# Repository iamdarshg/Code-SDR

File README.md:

# Code-SDR — V2 wideband SDR

A single-board, 100 MHz – 10 GHz receiver with an FPGA gateware datapath, an
RP2040 controller, and host-side tooling.

**Current hardware is V2:** the modular receiver/control board in
[`hardware/v2`](hardware/v2). The first-generation `Wideband-Test-V1` design was
audited and found **unsafe to fabricate**; its RTL, firmware, software and design
documents have been removed from this tree. What remains of V1 is the audit
record and clearly-labelled history — see
[V1 / legacy status](#v1--legacy-status).

> **Status, stated plainly.** No board has been fabricated and nothing in this
> repository has touched silicon. All gateware claims below are simulation and
> synthesis estimates. Frame counts, pin constraints and vendor I/O primitives
> still need Lattice Diamond and a first article. See
> [`GATEWARE.md`](GATEWARE.md), [`RESOURCE_REPORT.md`](RESOURCE_REPORT.md) and
> [`BRINGUP.md`](BRINGUP.md).

---

## Hardware at a glance

Source of truth is copper:
[`hardware/v2/Code-SDR-V2.kicad_pcb`](hardware/v2/Code-SDR-V2.kicad_pcb), parsed
in [`HARDWARE.md`](HARDWARE.md). 99 × 99 mm, four copper layers, 373 placed
footprints.

| Block | Part | Role |
|---|---|---|
| Controller | RP2040 (U10) + W25Q16JV QSPI flash | Sole controller: SPI master, FPGA config, USB CDC telemetry |
| FPGA | LIF-MD6000-6JMG80I (U20) | 5,936 LUT4, 180 kbit EBR, no DSP blocks |
| ADC | AD9215BCPZ-105 (U21) | 10-bit parallel, clocked from the fixed 100 MHz board reference — i.e. **100 MSPS**. `-105` is the part rating, not the operating rate |
| Ethernet | KSZ9031RNXCA (U30), RJ45 with magnetics | **RGMII only** — there is no GMII on this PCB |
| Reference | SiT8209 100 MHz (Y40) → CDCLVC1104 fanout | Shared ADC + synthesiser reference; PHY keeps its own 25 MHz crystal |
| Synthesisers | LMX2592 (U40), ADF4360-1 (U41) | First and second LO |
| RF front end | 5 SMA lanes, GRF LNAs, ADL5801 / LTC5548 / LT5560 mixers | 100 MHz – 10 GHz, 40 MHz real IBW, 2436.25 MHz IF1 → 26.25 MHz ADC IF |
| Power | 5 V in only (J1), TLV62569 bucks + TPS7A8300 LNA | ≈ 6.6 W estimated, ≈ 5 W of it the RF rail — see [`POWER.md`](POWER.md) |

USB on this board is **data/control only**; there is no USB-powered or USB-bulk
SDR streaming path.

## Gateware at a glance

Two **compile-time exclusive** modes (`v2_top` builds one or the other; the
RP2040 holds both bitstreams and swaps them over SPI in ~0.1–0.2 s):

```
MODE = 0 (raw)   ADC 100 MSPS -> 8/10-bit pack -> CDC FIFO -> UDP/IP -> MAC -> RGMII
MODE = 1 (fft)   ADC 100 MSPS -> CIC /R -> CDC FIFO -> window -> N-pt FFT
                             -> bin packetizer -> UDP/IP -> MAC -> RGMII
```

| | Raw (MODE=0) | FFT (MODE=1) |
|---|---|---|
| Area | **2,400 / 5,936 LUT4** (Yosys + ABC) | not yet measurable; bounded analytically |
| Verified throughput | 801 Mbps wire at 8-bit / 100 MSPS, no drops | 7.8 MSPS sustained input at N=1024 |
| Host does | FFT, demod, recording | display only |

10-bit at 100 MSPS offers 1002 Mbps, which no gigabit link carries, so raw mode
keeps the full rate and drops ~0.9 % of **whole datagrams** via a delta-sigma
accumulator (exact `floor(K·frac/65536)` drop count, verified to the packet). Loss
is counted and reported in-band, never hidden. Full detail, including the CIC /
FFT rate table and the three real FFT bugs found: [`GATEWARE.md`](GATEWARE.md).

## Repository map

| Path | What it is |
|---|---|
| `hardware/v2/` | **V2 board source of truth** — KiCad 9 project, 8 schematic sheets, footprints, deterministic generators in `tools/` |
| `hardware/redesign/` | Frequency plan, noise/filter budgets, power tree, V1↔V2 BOM cost model (reproducible Python) |
| `hardware/HARDWARE_VALIDATION.md` | Why V1 is DO NOT FABRICATE; the implemented V2 architecture |
| `hardware/validate_hardware.ps1` | Runs the ERC/DRC audit against the V2 project |
| `hardware/KSZ9031RNXCC-TR/`, `hardware/MABA-011108/` | Vendored KiCad vendor libraries (retained, see cleanup report) |
| `verilog/` | V2 gateware `v2_*.v`, testbenches, `v2_top.lpf`, `sim/crosslink_prims_sim.v` |
| `firmware/rp2040_dashboard/` | The RP2040 sketch: SPI telemetry, fault engine, bitstream swap |
| `software/` | Host tools: `sdr_spectrum.py`, `sdr_dashboard.py`, shared `sdr_common.py` |
| `tools/` | `run_tests.py`, `lint_verilog.py`, `check_firmware.py`, `gen_lpf.py`, `gen_twiddles.py`, `r2sdf_reference.py` |
| `tests/` | One retained cocotb test (`async_fifo`); the real regression is `tools/run_tests.py` |
| `docs/em-validation/` | EM/RF validation proof package (analytical, fail-closed) |
| `docs/superpowers/` | Routing plans and specs behind the V2 copper |
| `reviews/`, `outputs/code-sdr-routing/` | V2 routing review records and routing deliverables |
| `openfpga_framework/` | Vendored upstream OpenFPGA framework — retained, not used by the V2 build (see cleanup report) |
| `HARDWARE.md` / `GATEWARE.md` / `RESOURCE_REPORT.md` / `POWER.md` / `BRINGUP.md` / `KNOWN_ISSUES.md` | PCB-parse, gateware, area, power, bring-up and defect register |
| `docs/CLEANUP_2026-11-04.md` | The V1 removal / README cleanup record |

## Quick start

Requirements: Python 3.8+ with `numpy scipy matplotlib` for the host tools;
Icarus Verilog for the RTL regression; Verilator for the lint gate; `arduino-cli`
with the earlephilhower RP2040 core for the firmware build.

```bash
pip install numpy scipy matplotlib

# Host viewer — works with no radio attached
python software/sdr_spectrum.py --simulate --save spectrum.png --frames 20

# Live, against a configured board (both modes transmit to UDP 10000)
python software/sdr_spectrum.py --mode raw
python software/sdr_spectrum.py --mode fft
python software/sdr_dashboard.py --port 10000 --serial COM7

# Host-tool unit checks (run from the repository root)
python software/test_dashboard.py
```

## Verification

These are the gates CI runs (`.github/workflows/rtl.yml`), and they are the only
commands that should be quoted as "the tests pass":

```bash
python tools/run_tests.py        # Icarus regression: 21 testbench runs
python tools/lint_verilog.py     # Verilator lint: 5 tops
python tools/check_firmware.py   # arduino-cli compile of the RP2040 sketch
```

Last run of this tree (2026-11-04, Windows, Icarus Verilog 12.0, Verilator 5.040,
arduino-cli):

```
run_tests.py       21/21 passed
lint_verilog.py    5/5 tops clean
check_firmware.py  PASS: firmware compiles (0 warning(s))
```

Hardware analyses are reproducible too:

```bash
python hardware/redesign/validate_plan.py    # frequency plan / LO / Nyquist
python hardware/redesign/rf_analysis.py      # Friis cascade, NF, anti-alias
python hardware/redesign/cost_model.py       # V1 vs V2 fitted BOM
python tools/gen_lpf.py                      # PCB -> verilog/v2_top_generated.lpf
```

## Documentation

| Document | Contents |
|---|---|
| [`HARDWARE.md`](HARDWARE.md) | Every claim parsed from placed footprints, pad nets and PCB setup; supersedes all other hardware prose |
| [`hardware/HARDWARE_VALIDATION.md`](hardware/HARDWARE_VALIDATION.md) | V1 audit (ERC/DRC counts), V2 corrections, limitations, first-article plan |
| [`GATEWARE.md`](GATEWARE.md) | Two modes, rate plan, throughput table, FFT correctness, what blocks production |
| [`RESOURCE_REPORT.md`](RESOURCE_REPORT.md) | Yosys/ABC area numbers and what is still unmeasured |
| [`POWER.md`](POWER.md) | Per-rail load estimates and the one-lane-at-a-time policy |
| [`BRINGUP.md`](BRINGUP.md) | Staged board bring-up, each step with its failure signature |
| [`KNOWN_ISSUES.md`](KNOWN_ISSUES.md) | Defect register: fixed (kept for the record) and open |
| [`docs/em-validation/EM_VALIDATION_REPORT.md`](docs/em-validation/EM_VALIDATION_REPORT.md) | EM/RF evidence package; every full-wave/physical claim fails closed |
| [`software/LEGACY.md`](software/LEGACY.md) | What the four removed V1 software trees attempted |

## V1 / legacy status

The first-generation design (`Wideband-Test-V1`, dsPIC33 firmware, 105 MSPS /
GMII RTL, USB-bulk host stack, GNU Radio module, ExtIO plugin) is **removed from
this tree**. It is not supported, not buildable here, and its pin, clock and
interface claims must not be reused: see the void list at the top of
[`HARDWARE.md`](HARDWARE.md).

Where the record survives:

- `hardware/HARDWARE_VALIDATION.md` — the reproducible V1 audit, kept as evidence.
- [`software/LEGACY.md`](software/LEGACY.md) — what each removed software tree
  attempted and why it was abandoned.
- [`KNOWN_ISSUES.md`](KNOWN_ISSUES.md) § Removed — the deleted P0 RTL cluster,
  module by module.
- [`ISSUE_11_VERIFICATION_REPORT.md`](ISSUE_11_VERIFICATION_REPORT.md) — the V1
  integration report, retained but marked historical.
- `git log -- <path>` — every removed tree is recoverable from history.
- [`docs/CLEANUP_2026-11-04.md`](docs/CLEANUP_2026-11-04.md) — the itemised
  removal list from the 2026-11-04 cleanup.

Deliberately **not** removed: vendored third-party libraries and the upstream
OpenFPGA framework, which are not V1 design work. They are classified in the
cleanup report.

## Licence

This repository contains **no `LICENSE` file**. Treat it as all rights reserved
until one is added; the badges and MIT text that earlier revisions of this README
carried referred to a file that is not present.

## References

- Lattice CrossLink: FPGA-TN-02015 (sysCLOCK PLL), FPGA-TN-02016 (sysI/O),
  FPGA-TN-02012 (high-speed I/O) — needed to confirm the vendor primitives that
  `verilog/v2_clock_pll.v` and `verilog/v2_rgmii.v` instantiate behind
  `V2_USE_VENDOR_PLL` / `V2_USE_VENDOR_DDR`.
- Microchip KSZ9031RNX datasheet — RGMII delay registers used by
  `v2_phy_manager.v`.
- Analog Devices AD9215 datasheet — 10-bit parallel timing.

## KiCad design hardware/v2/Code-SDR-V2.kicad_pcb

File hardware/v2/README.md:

# Code-SDR V2 hardware

This is the modular KiCad 9 receiver/control-board redesign. It covers
100 MHz-10 GHz with 40 MHz useful real bandwidth. It is explicitly not an ESC;
the ESC remains a separate external board.

## Project structure

- `Code-SDR-V2.kicad_sch` - hierarchical root schematic.
- `sheets/` - eight functional subsheets.
- `Code-SDR-V2.kicad_pcb` - 99 x 99 mm, four-layer PCB with the 49 RF50
  controlled-impedance nets routed.
- `Code-SDR-V2.kicad_pro` and `.kicad_dru` - project and enforced rules.
- `CodeSDR.pretty/` and `CodeSDR.kicad_sym` - project-local audited libraries.
- `tools/design_model.py` - single electrical component/net contract.
- `tools/generate_schematic.py` and `tools/generate_pcb.py` - deterministic CAD
  generation.
- `build/` - validation and intermediate output; final manufacturing outputs
  are exported separately for release.

The FPGA supply islands and configuration pulls implement the Lattice
CrossLink hardware checklist: used VCC, VCCGPLL, VCCAUX and each VCCIO bank
are locally filtered and bypassed, while the unused D-PHY supply groups are
intentionally unpowered. CRESET_B, CDONE and SPI_SS have 4.7 kΩ pull-ups to
VCCIO0 and the processor-driven SPI clock is source damped.

## Regeneration

```powershell
python hardware/v2/tools/generate_schematic.py
& "C:\Program Files\KiCad\9.0\bin\python.exe" hardware/v2/tools/generate_pcb.py
kicad-cli sch erc --format json -o hardware/v2/build/erc.json hardware/v2/Code-SDR-V2.kicad_sch
kicad-cli pcb drc --format json --all-track-errors -o hardware/v2/build/drc.json hardware/v2/Code-SDR-V2.kicad_pcb
```

Regeneration intentionally replaces the PCB with the clean placement baseline:
344 footprints, four copper layers, and the two internal ground-reference zones.
Do not run `generate_pcb.py` after beginning a manual route unless that route
is meant to be discarded.

## Route import and release

Freerouting must write its completed session to
`build/Code-SDR-V2-routed.ses`. Then run:

```powershell
java -Xmx2600m -jar freerouting-2.2.4.jar `
  -de hardware/v2/build/Code-SDR-V2.dsn `
  -do hardware/v2/build/Code-SDR-V2-routed.ses `
  -mp 1 -mt 0 -da -dct 1 --gui.enabled=false
python hardware/v2/tools/sanitize_route_session.py
& "C:\Program Files\KiCad\9.0\bin\python.exe" hardware/v2/tools/import_route.py
& "C:\Program Files\KiCad\9.0\bin\python.exe" hardware/v2/tools/export_route_checkpoint.py
& "C:\Program Files\KiCad\9.0\bin\python.exe" hardware/v2/tools/refill_zones.py
& "C:\Program Files\KiCad\9.0\bin\python.exe" hardware/v2/tools/add_rf_via_fences.py
& "C:\Program Files\KiCad\9.0\bin\python.exe" hardware/v2/tools/validate_route.py
powershell -ExecutionPolicy Bypass -File hardware/v2/tools/export_release.ps1
```

The four-layer routing contract is `F.Cu / solid In1 GND / solid In2 GND /
B.Cu`. The 49 RF50 nets are routed as nominal 50-ohm microstrip on the two
outer layers using 0.23 mm traces over a 0.13 mm dielectric. F.Cu is preferred;
B.Cu is used only for four unavoidable crossings, with a nearby ground-return
via at every layer transition. All remaining digital, power and slow nets are
intentionally unrouted for completion in KiCad. No signal trace may cut either
internal reference plane.
Use one persisted pass at a time: import each normally completed session,
run DRC, export the routed board with `export_route_checkpoint.py`, and repeat
until KiCad reports no opens. `-mt 0` lets Freerouting select the available
worker-thread count. Add the fences and run length/skew validation only
after importing the completed clean-board route.

`import_route.py` also refreshes footprint hierarchy paths from the current
schematic before parity checking. Route-validation helpers must enforce the
four-layer contract above before manufacturing output is accepted.

## Non-CAD release gates

The specified 0.13 mm outer dielectric and nominal 0.23 mm RF trace are the
50-ohm impedance-design basis. Have the
selected fabricator field-solve RF and differential geometries using its actual
Dk, copper and solder mask. A first article must pass the VNA, PLL, NF,
linearity, image, thermal and full-range calibration plan in
[`../HARDWARE_VALIDATION.md`](../HARDWARE_VALIDATION.md).

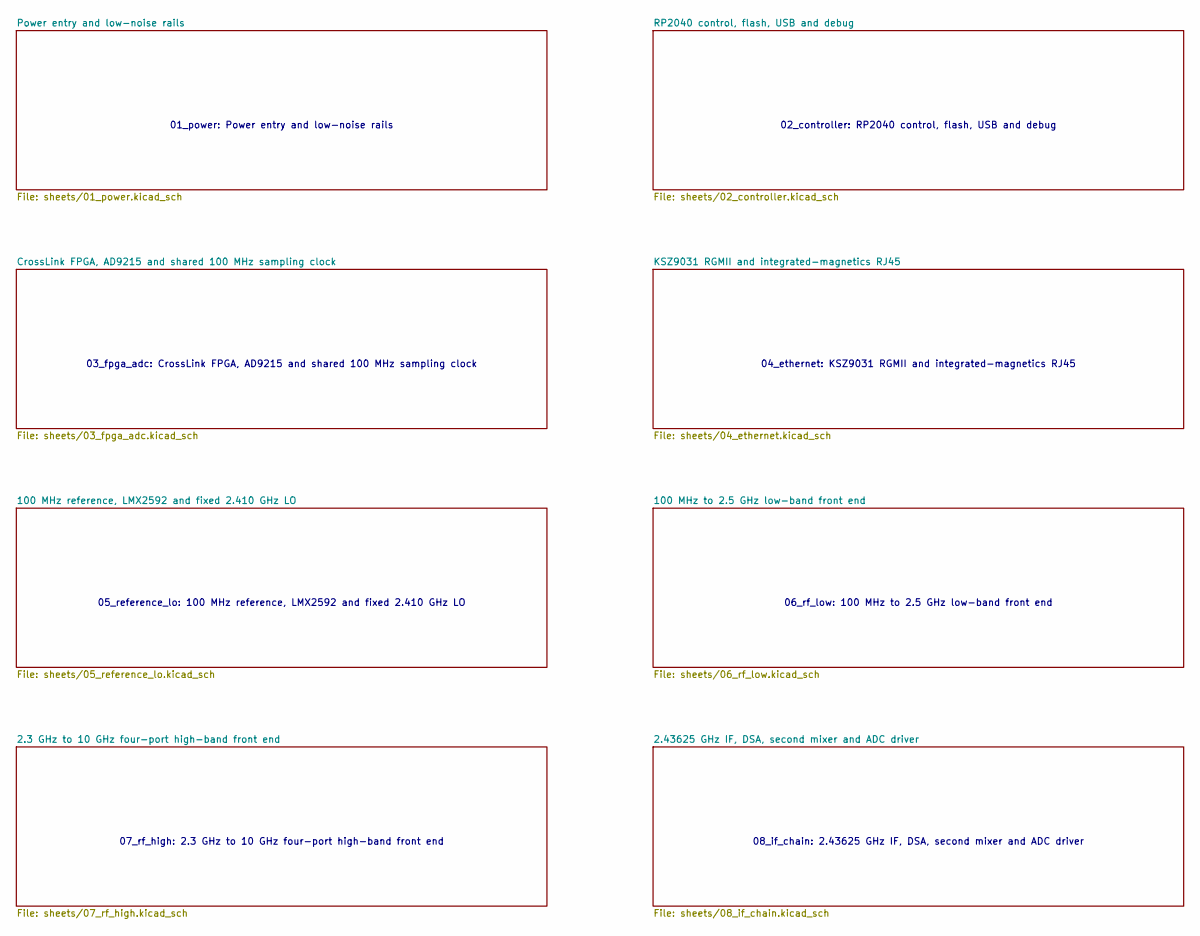
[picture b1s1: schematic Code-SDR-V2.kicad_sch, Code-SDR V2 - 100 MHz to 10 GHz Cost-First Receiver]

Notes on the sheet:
01_power: Power entry and low-noise rails
02_controller: RP2040 control, flash, USB and debug
03_fpga_adc: CrossLink FPGA, AD9215 and shared 100 MHz sampling clock
04_ethernet: KSZ9031 RGMII and integrated-magnetics RJ45
05_reference_lo: 100 MHz reference, LMX2592 and fixed 2.410 GHz LO
06_rf_low: 100 MHz to 2.5 GHz low-band front end
07_rf_high: 2.3 GHz to 10 GHz four-port high-band front end
08_if_chain: 2.43625 GHz IF, DSA, second mixer and ADC driver

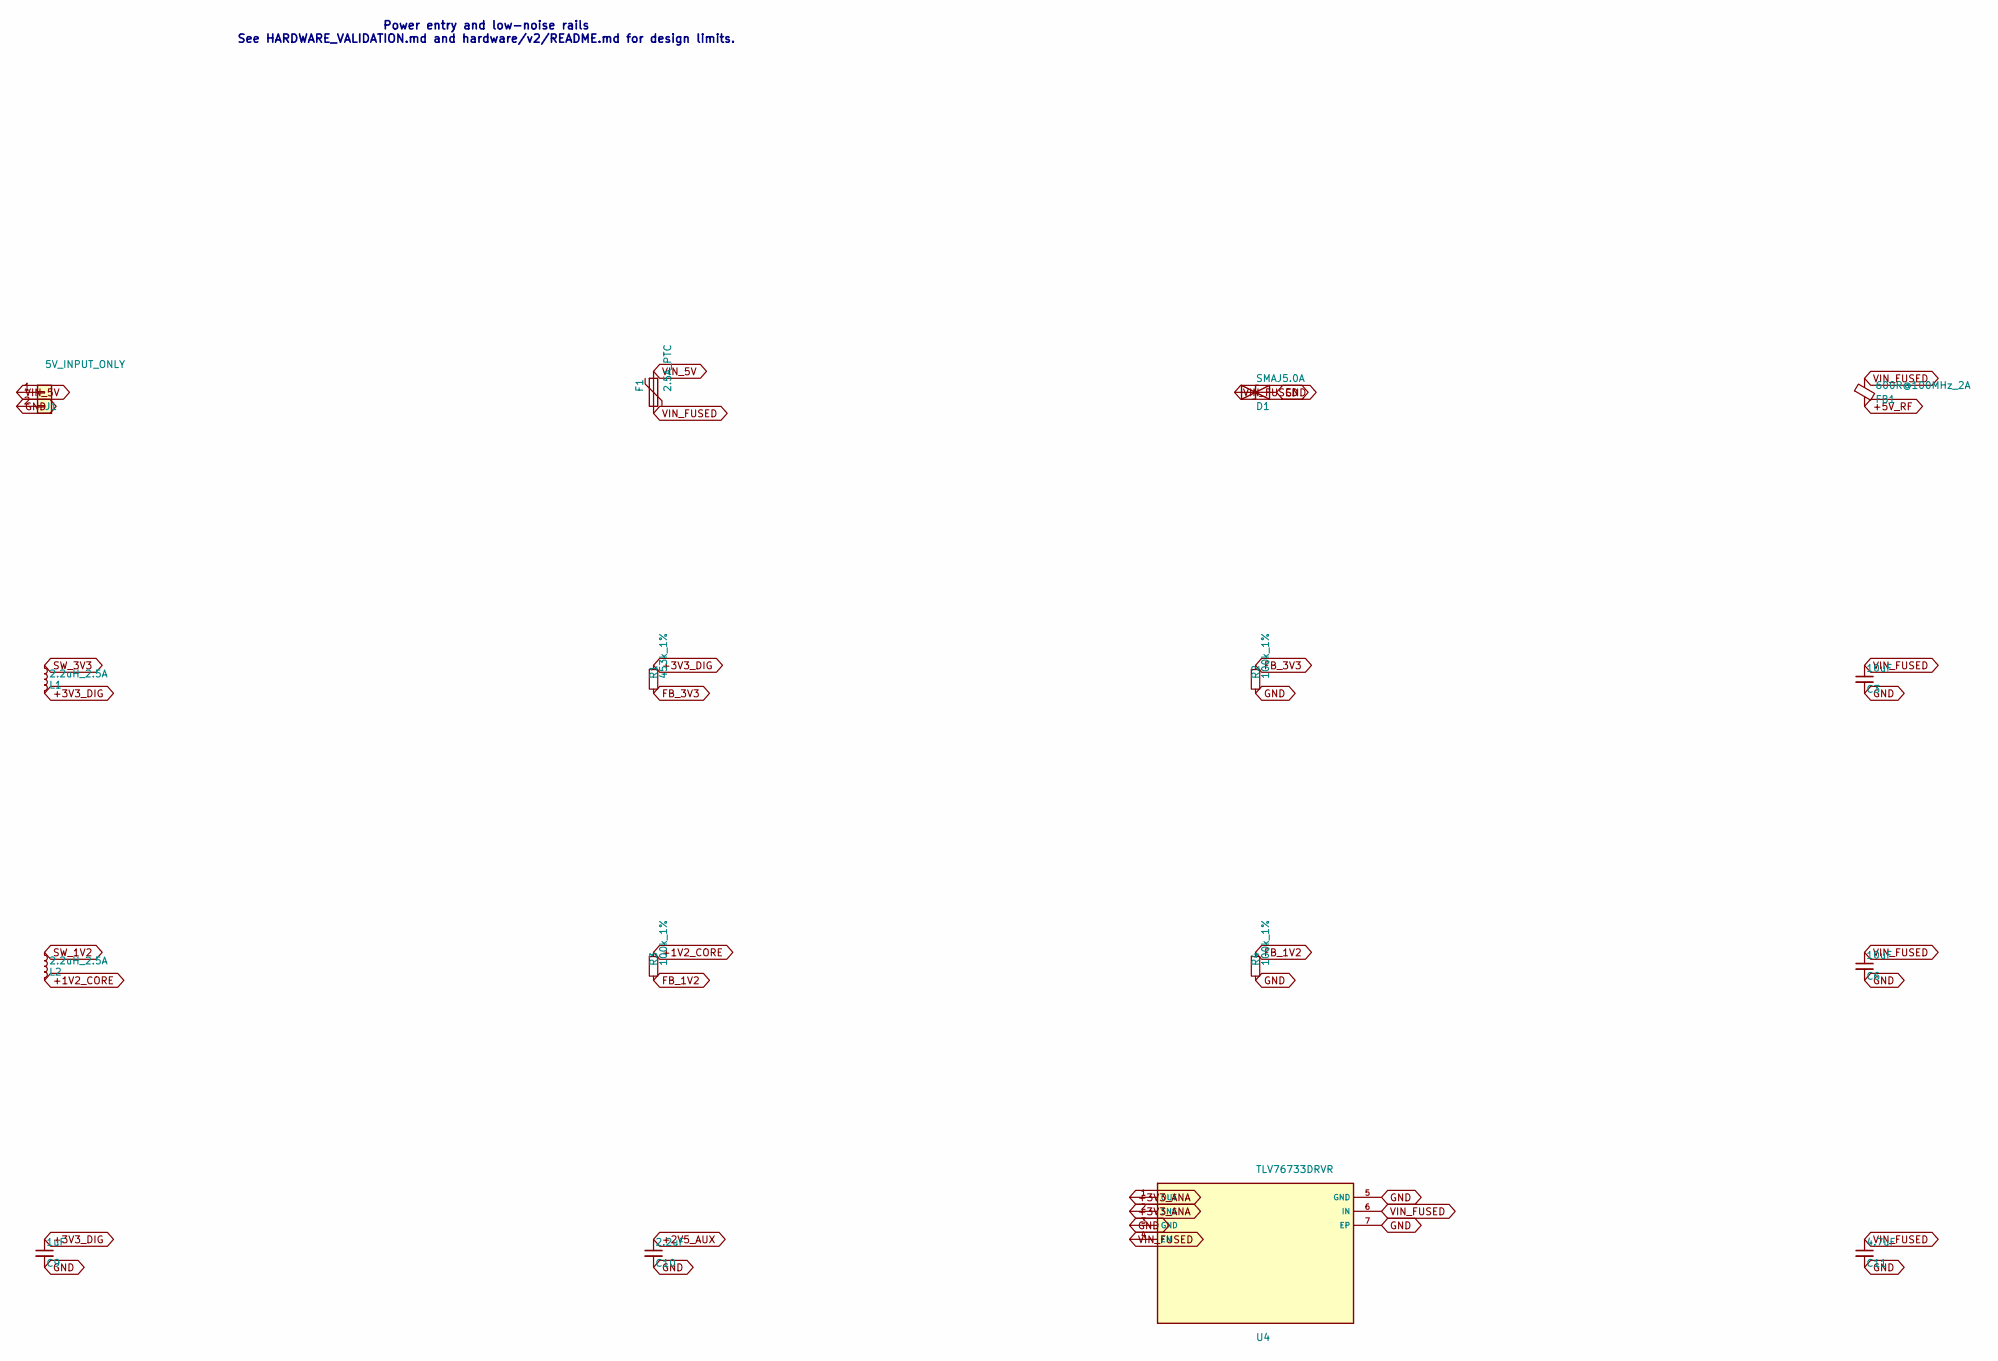
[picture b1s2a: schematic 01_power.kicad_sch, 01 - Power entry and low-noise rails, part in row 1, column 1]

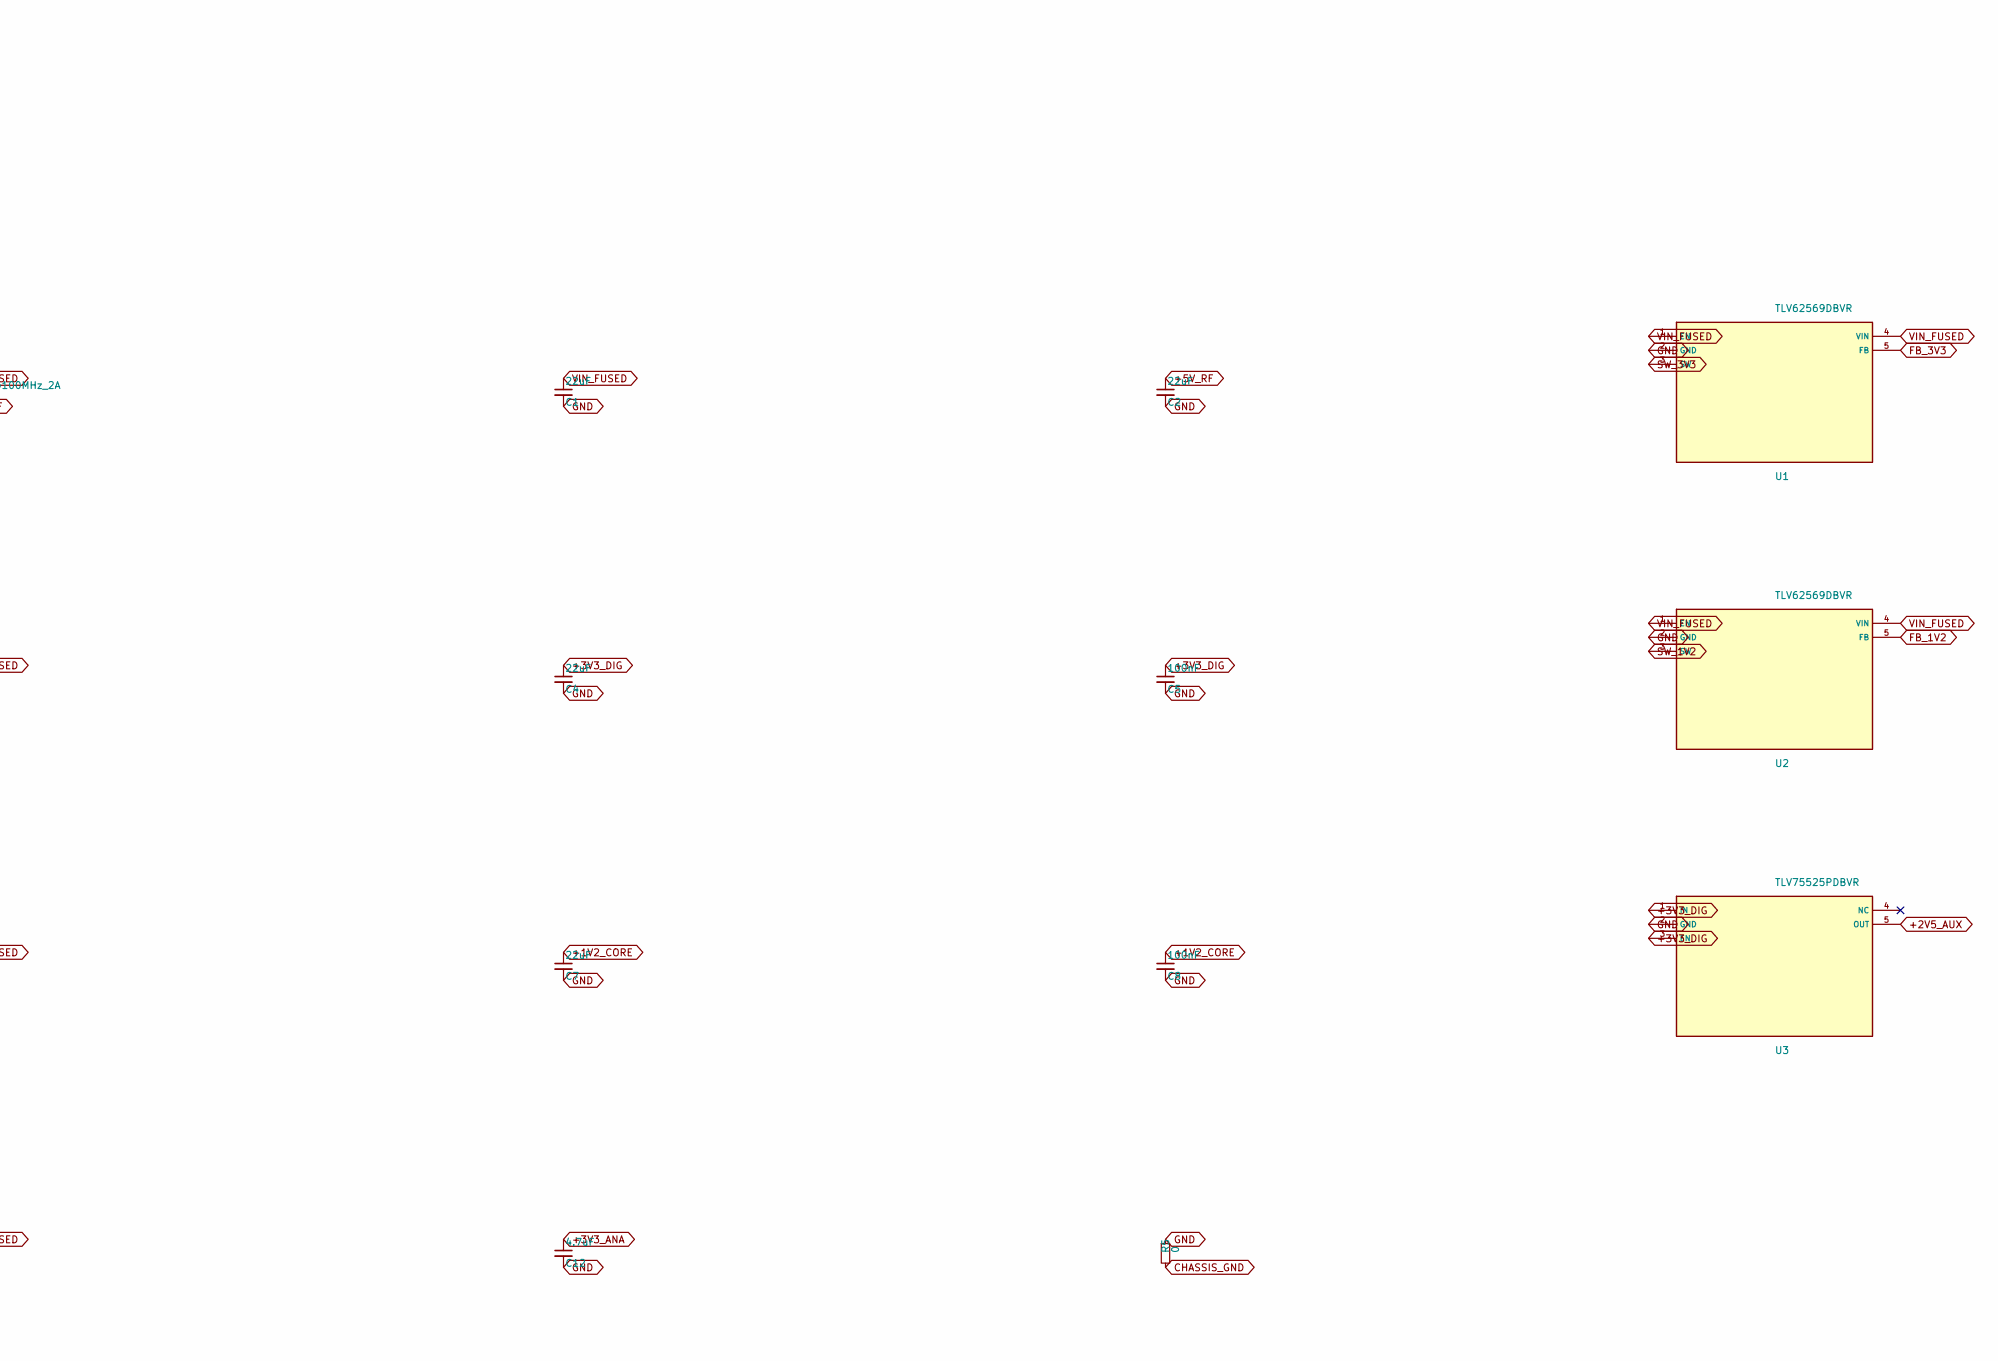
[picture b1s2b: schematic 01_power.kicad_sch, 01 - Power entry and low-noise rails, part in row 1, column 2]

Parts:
C1, C2, C4, C7: 22uF; C_0805_2012Metric
C3, C6: 10uF; C_0805_2012Metric
C5, C8: 100nF; C_0402_1005Metric
C9: 1uF; C_0603_1608Metric
C10: 2.2uF; C_0603_1608Metric
C11, C12: 4.7uF; C_0805_2012Metric
D1: SMAJ5.0A; D_SMA
F1: 2.5A_PTC; Fuse_1812_4532Metric
FB1: 600R@100MHz_2A; Inductor_0805_HandSolder
J1: 5V_INPUT_ONLY; TerminalBlock_Phoenix_MKDS-1,5-2_1x02_P5.00mm_Horizontal
L1, L2: 2.2uH_2.5A; Inductor_0805_HandSolder
R1: 453k_1%; R_0402_1005Metric
R2, R3, R4: 100k_1%; R_0402_1005Metric
R5: 0; R_0603_1608Metric
U1, U2: TLV62569DBVR; SOT-23-5
U3: TLV75525PDBVR; SOT-23-5
U4: TLV76733DRVR; WSON-6-1EP_2x2mm_P0.65mm_EP1x1.6mm_ThermalVias

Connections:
+1V2_CORE: C7.1, C8.1, L2.2, R3.1; also elsewhere on the board
+2V5_AUX: C10.1, U3.5 (OUT); also elsewhere on the board
+3V3_ANA: C12.1, U4.1 (OUT), U4.2 (SNS), U4.19, U4.20; also elsewhere on the board
+5V_RF: C2.1, FB1.2; also elsewhere on the board
ANA_NR_SS: U4.13; also elsewhere on the board
CHASSIS_GND: R5.2; also elsewhere on the board
FB_1V2: R3.2, R4.1, U2.5 (FB)
FB_3V3: R1.2, R2.1, U1.5 (FB)
SW_1V2: L2.1, U2.3 (SW)
SW_3V3: L1.1, U1.3 (SW)
VIN_5V: F1.1, J1.1

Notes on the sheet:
Power entry and low-noise rails See HARDWARE_VALIDATION.md and hardware/v2/README.md for design limits.

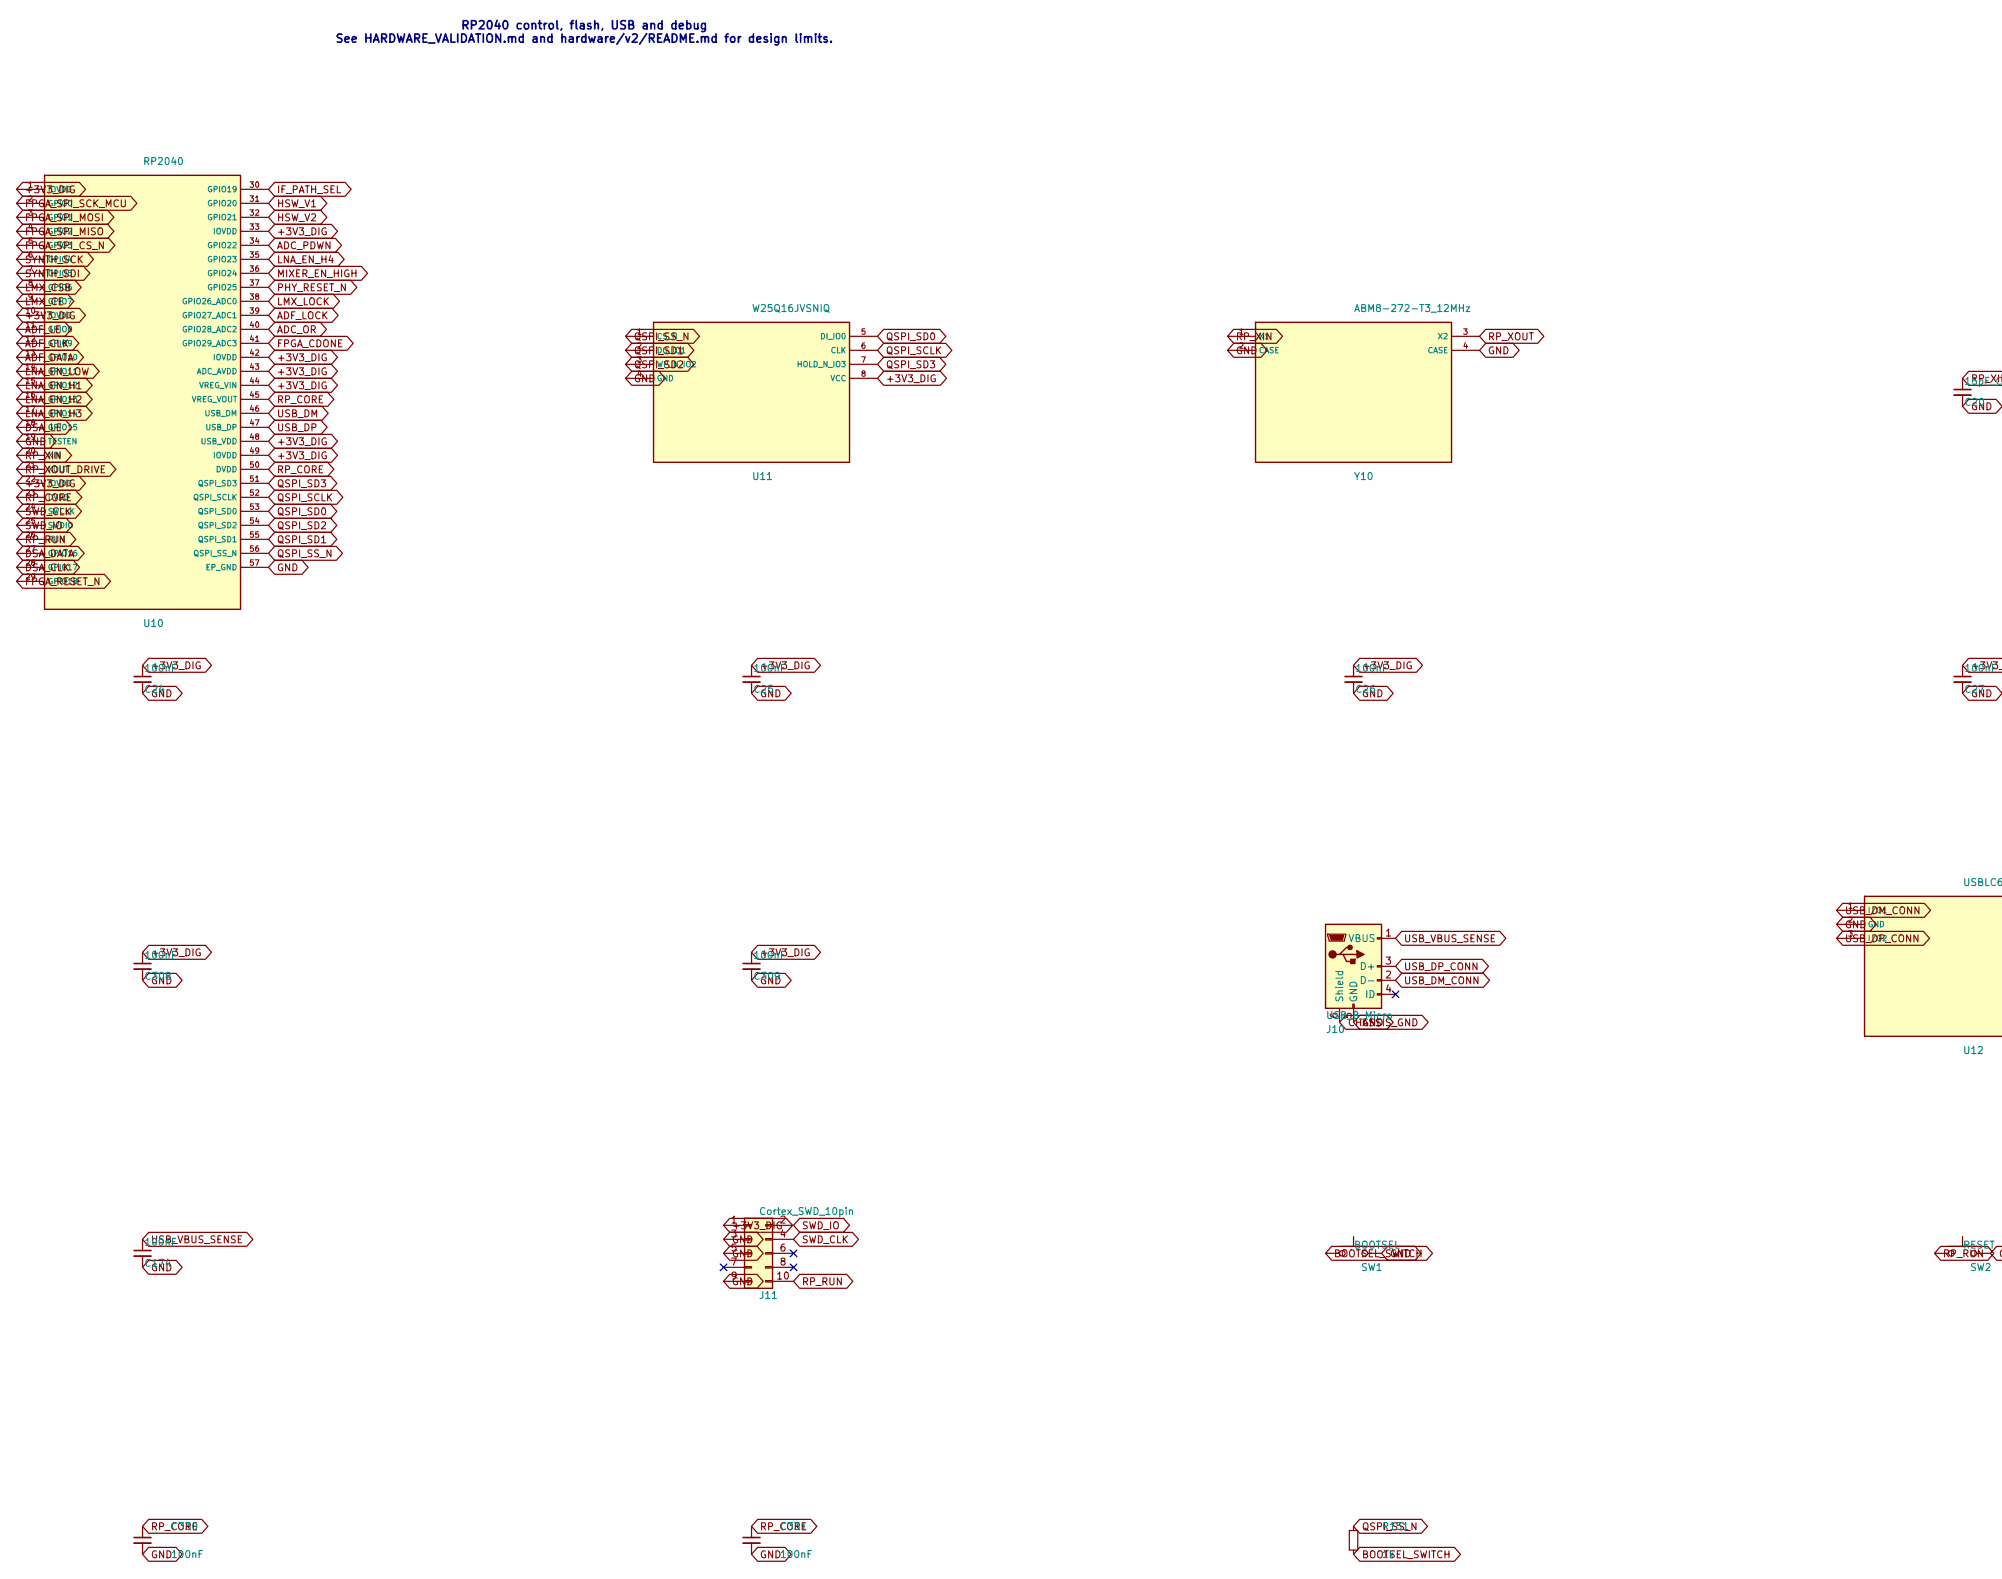
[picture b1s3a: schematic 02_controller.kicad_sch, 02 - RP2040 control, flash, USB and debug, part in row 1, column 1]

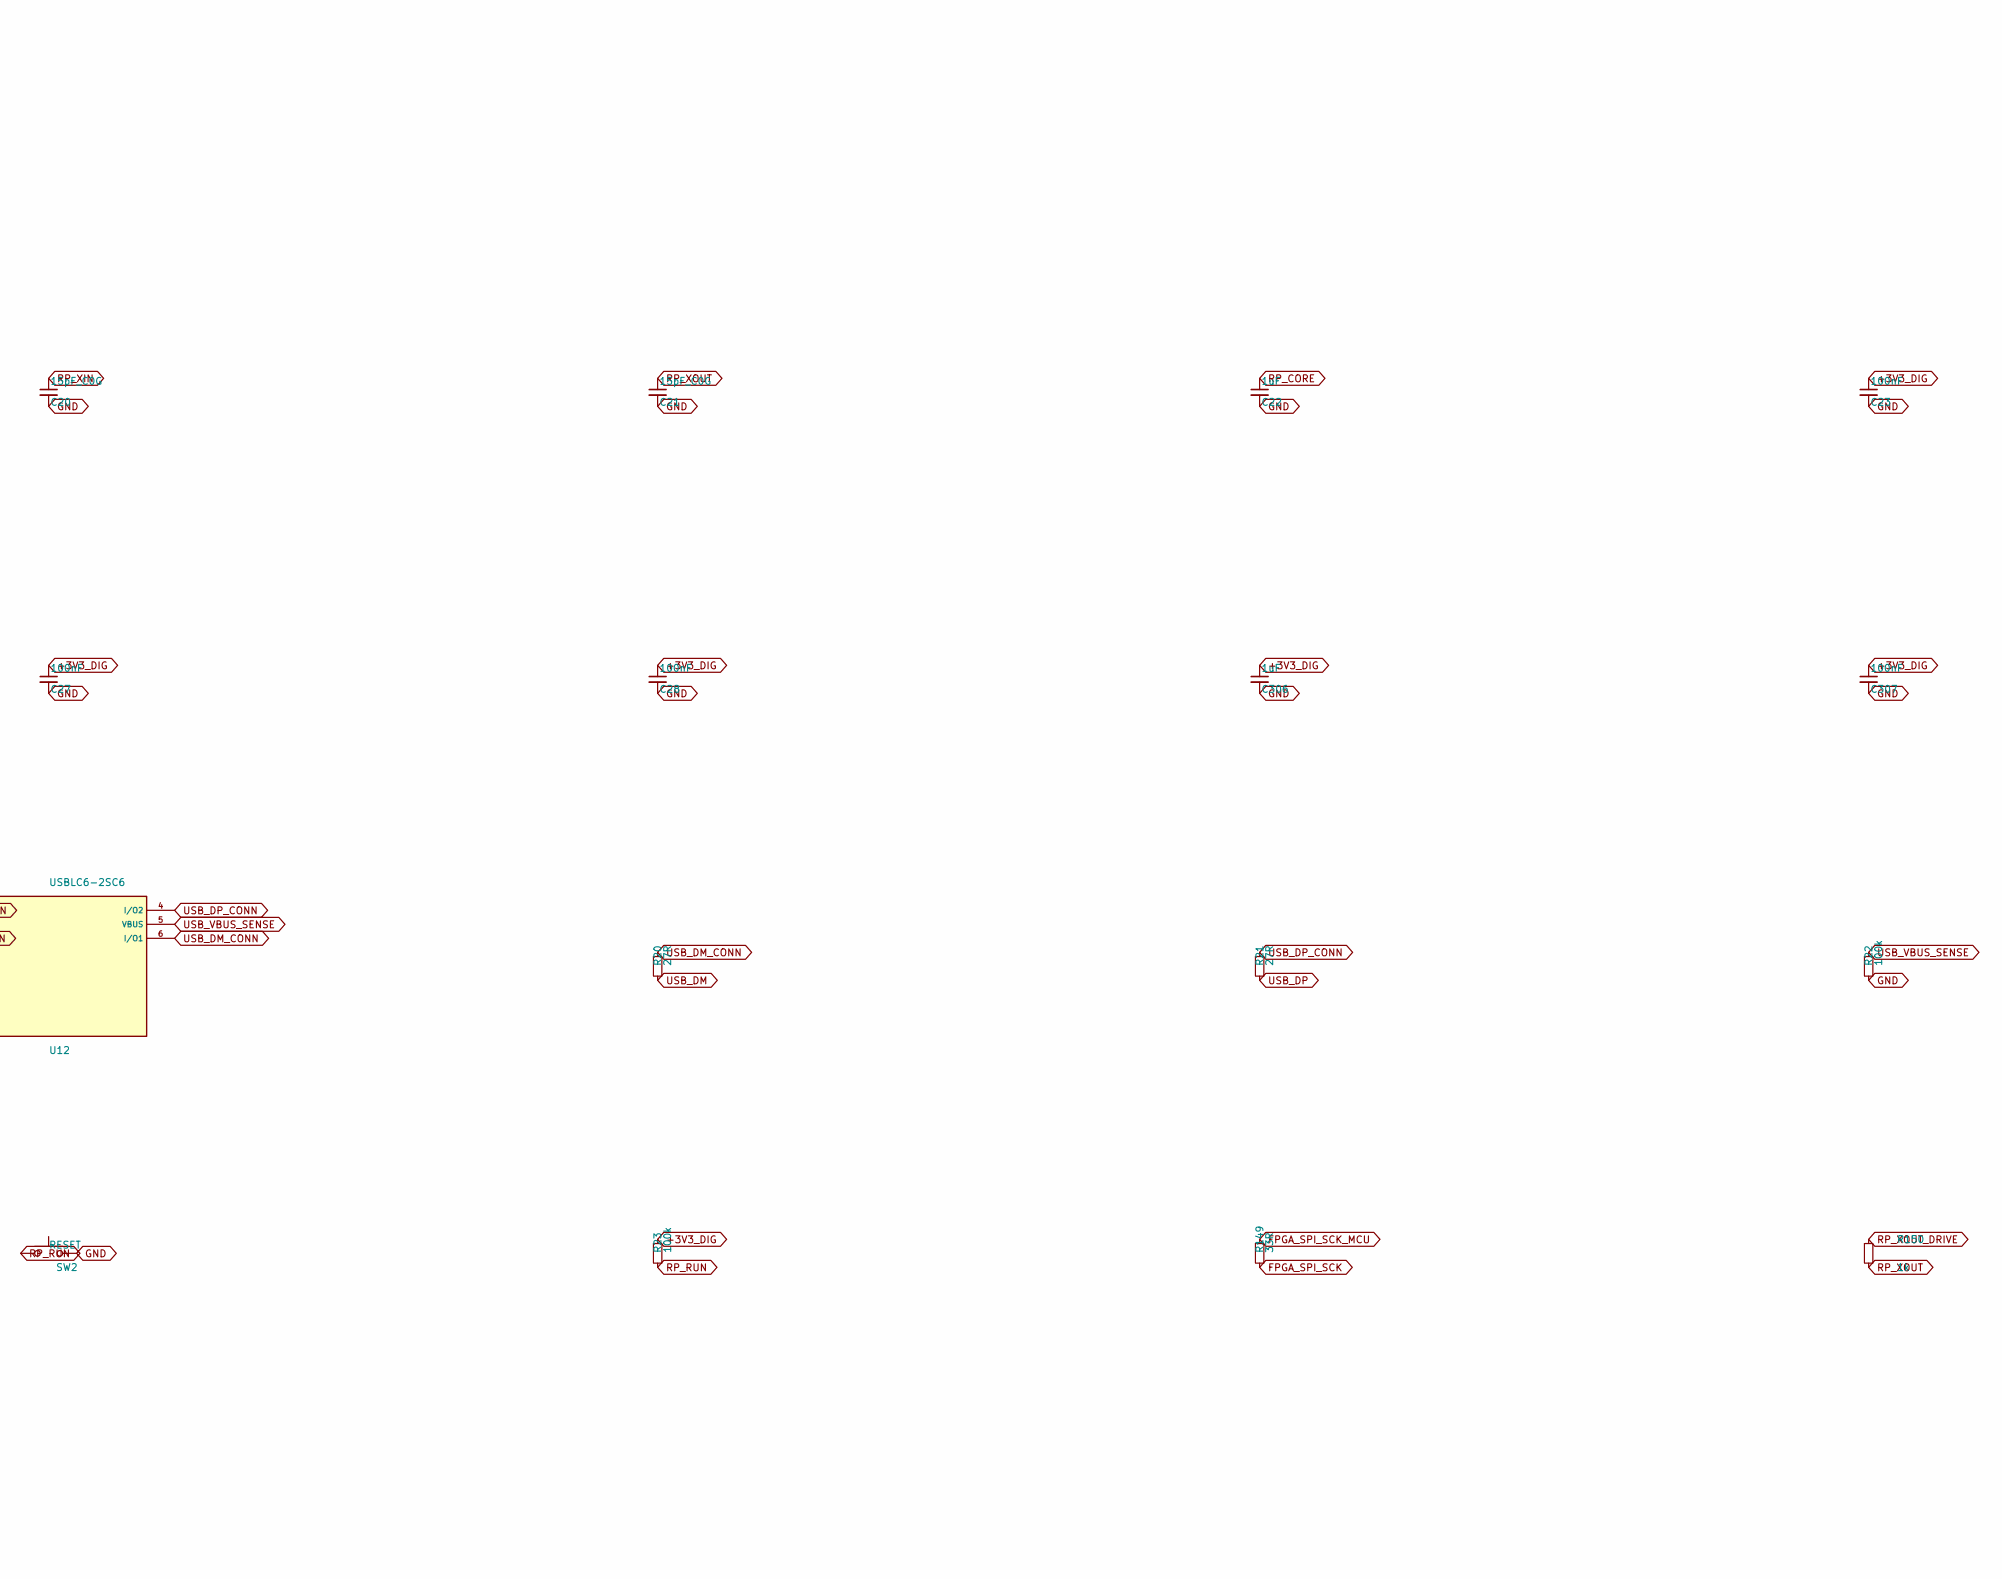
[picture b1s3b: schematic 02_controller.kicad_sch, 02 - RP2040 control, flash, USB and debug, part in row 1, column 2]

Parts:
C20, C21: 15pF_C0G; C_0402_1005Metric
C22: 1uF; C_0603_1608Metric
C23, C24, C25, C26, C27, C28, C174, C307, C308, C309, C330, C331: 100nF; C_0402_1005Metric
C306: 1uF; C_0402_1005Metric
J10: USB_B_Micro; USB_Micro-B_Molex-105017-0001
J11: Cortex_SWD_10pin; PinHeader_2x05_P1.27mm_Vertical
R20, R21: 27R; R_0402_1005Metric
R22, R23: 100k; R_0402_1005Metric
R149: 33R; R_0402_1005Metric
R150: 1k; R_0201_0603Metric
R151: 1k; R_0402_1005Metric
SW1: BOOTSEL; SW_SPST_TL3342
SW2: RESET; SW_SPST_TL3342
U10: RP2040; QFN-56-1EP_7x7mm_P0.4mm_EP3.2x3.2mm_ThermalVias
U11: W25Q16JVSNIQ; SOIC-8_3.9x4.9mm_P1.27mm
U12: USBLC6-2SC6; SOT-23-6
Y10: ABM8-272-T3_12MHz; Crystal_SMD_3225-4Pin_3.2x2.5mm

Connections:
ADC_OR: U10.40 (GPIO28_ADC2); also elsewhere on the board
ADC_PDWN: U10.34 (GPIO22); also elsewhere on the board
ADF_CLK: U10.12 (GPIO9); also elsewhere on the board
ADF_DATA: U10.13 (GPIO10); also elsewhere on the board
ADF_LE: U10.11 (GPIO8); also elsewhere on the board
ADF_LOCK: U10.39 (GPIO27_ADC1); also elsewhere on the board
BOOTSEL_SWITCH: R151.2, SW1.1
CHASSIS_GND: J10.6 (Shield); also elsewhere on the board
DSA_CLK: U10.28 (GPIO17); also elsewhere on the board
DSA_DATA: U10.27 (GPIO16); also elsewhere on the board
DSA_LE: U10.18 (GPIO15); also elsewhere on the board
FPGA_CDONE: U10.41 (GPIO29_ADC3); also elsewhere on the board
FPGA_RESET_N: U10.29 (GPIO18); also elsewhere on the board
FPGA_SPI_CS_N: U10.5 (GPIO3); also elsewhere on the board
FPGA_SPI_MISO: U10.4 (GPIO2); also elsewhere on the board
FPGA_SPI_MOSI: U10.3 (GPIO1); also elsewhere on the board
FPGA_SPI_SCK: R149.2; also elsewhere on the board
FPGA_SPI_SCK_MCU: R149.1, U10.2 (GPIO0)
HSW_V1: U10.31 (GPIO20); also elsewhere on the board
HSW_V2: U10.32 (GPIO21); also elsewhere on the board
IF_PATH_SEL: U10.30 (GPIO19); also elsewhere on the board
LMX_CE: U10.9 (GPIO7); also elsewhere on the board
LMX_CSB: U10.8 (GPIO6); also elsewhere on the board
LMX_LOCK: U10.38 (GPIO26_ADC0); also elsewhere on the board
LNA_EN_H1: U10.15 (GPIO12); also elsewhere on the board
LNA_EN_H2: U10.16 (GPIO13); also elsewhere on the board
LNA_EN_H3: U10.17 (GPIO14); also elsewhere on the board
LNA_EN_H4: U10.35 (GPIO23); also elsewhere on the board
LNA_EN_LOW: U10.14 (GPIO11); also elsewhere on the board
MIXER_EN_HIGH: U10.36 (GPIO24); also elsewhere on the board
PHY_RESET_N: U10.37 (GPIO25); also elsewhere on the board
QSPI_SCLK: U10.52 (QSPI_SCLK), U11.6 (CLK)
QSPI_SD0: U10.53 (QSPI_SD0), U11.5 (DI_IO0)
QSPI_SD1: U10.55 (QSPI_SD1), U11.2 (DO_IO1)
QSPI_SD2: U10.54 (QSPI_SD2), U11.3 (WP_N_IO2)
QSPI_SD3: U10.51 (QSPI_SD3), U11.7 (HOLD_N_IO3)
QSPI_SS_N: R151.1, U10.56 (QSPI_SS_N), U11.1 (CS_N)
RP_CORE: C22.1, C330.1, C331.1, U10.23 (DVDD), U10.45 (VREG_VOUT), U10.50 (DVDD)
RP_RUN: J11.10, R23.2, SW2.1, U10.26 (RUN)
RP_XIN: C20.1, U10.20 (XIN), Y10.1 (X1)
RP_XOUT: C21.1, R150.2, Y10.3 (X2)
RP_XOUT_DRIVE: R150.1, U10.21 (XOUT)
SWD_CLK: J11.4, U10.24 (SWCLK)
SWD_IO: J11.2, U10.25 (SWDIO)
SYNTH_SCK: U10.6 (GPIO4); also elsewhere on the board
SYNTH_SDI: U10.7 (GPIO5); also elsewhere on the board
USB_DM: R20.2, U10.46 (USB_DM)
USB_DM_CONN: J10.2 (D-), R20.1, U12.1 (I/O1), U12.6 (I/O1)
USB_DP: R21.2, U10.47 (USB_DP)
USB_DP_CONN: J10.3 (D+), R21.1, U12.3 (I/O2), U12.4 (I/O2)
USB_VBUS_SENSE: C174.1, J10.1 (VBUS), R22.1, U12.5 (VBUS)

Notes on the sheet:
RP2040 control, flash, USB and debug See HARDWARE_VALIDATION.md and hardware/v2/README.md for design limits.
